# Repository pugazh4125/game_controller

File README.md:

here in this project i have designed my own game controller i wanted to buy a game controller like xbox or ps3 controller but i cant afford those so then began to think how about designing my own controller and that's  how this project was began also doing this project i learnt multi layer pcb designing and also something power traces and signal traces where the traces have to get importantly designed so i learnt them also this project was not completed 100% at first i thought i completed it but i didn't i have to make some changes so i will update this repo once i completed the changes

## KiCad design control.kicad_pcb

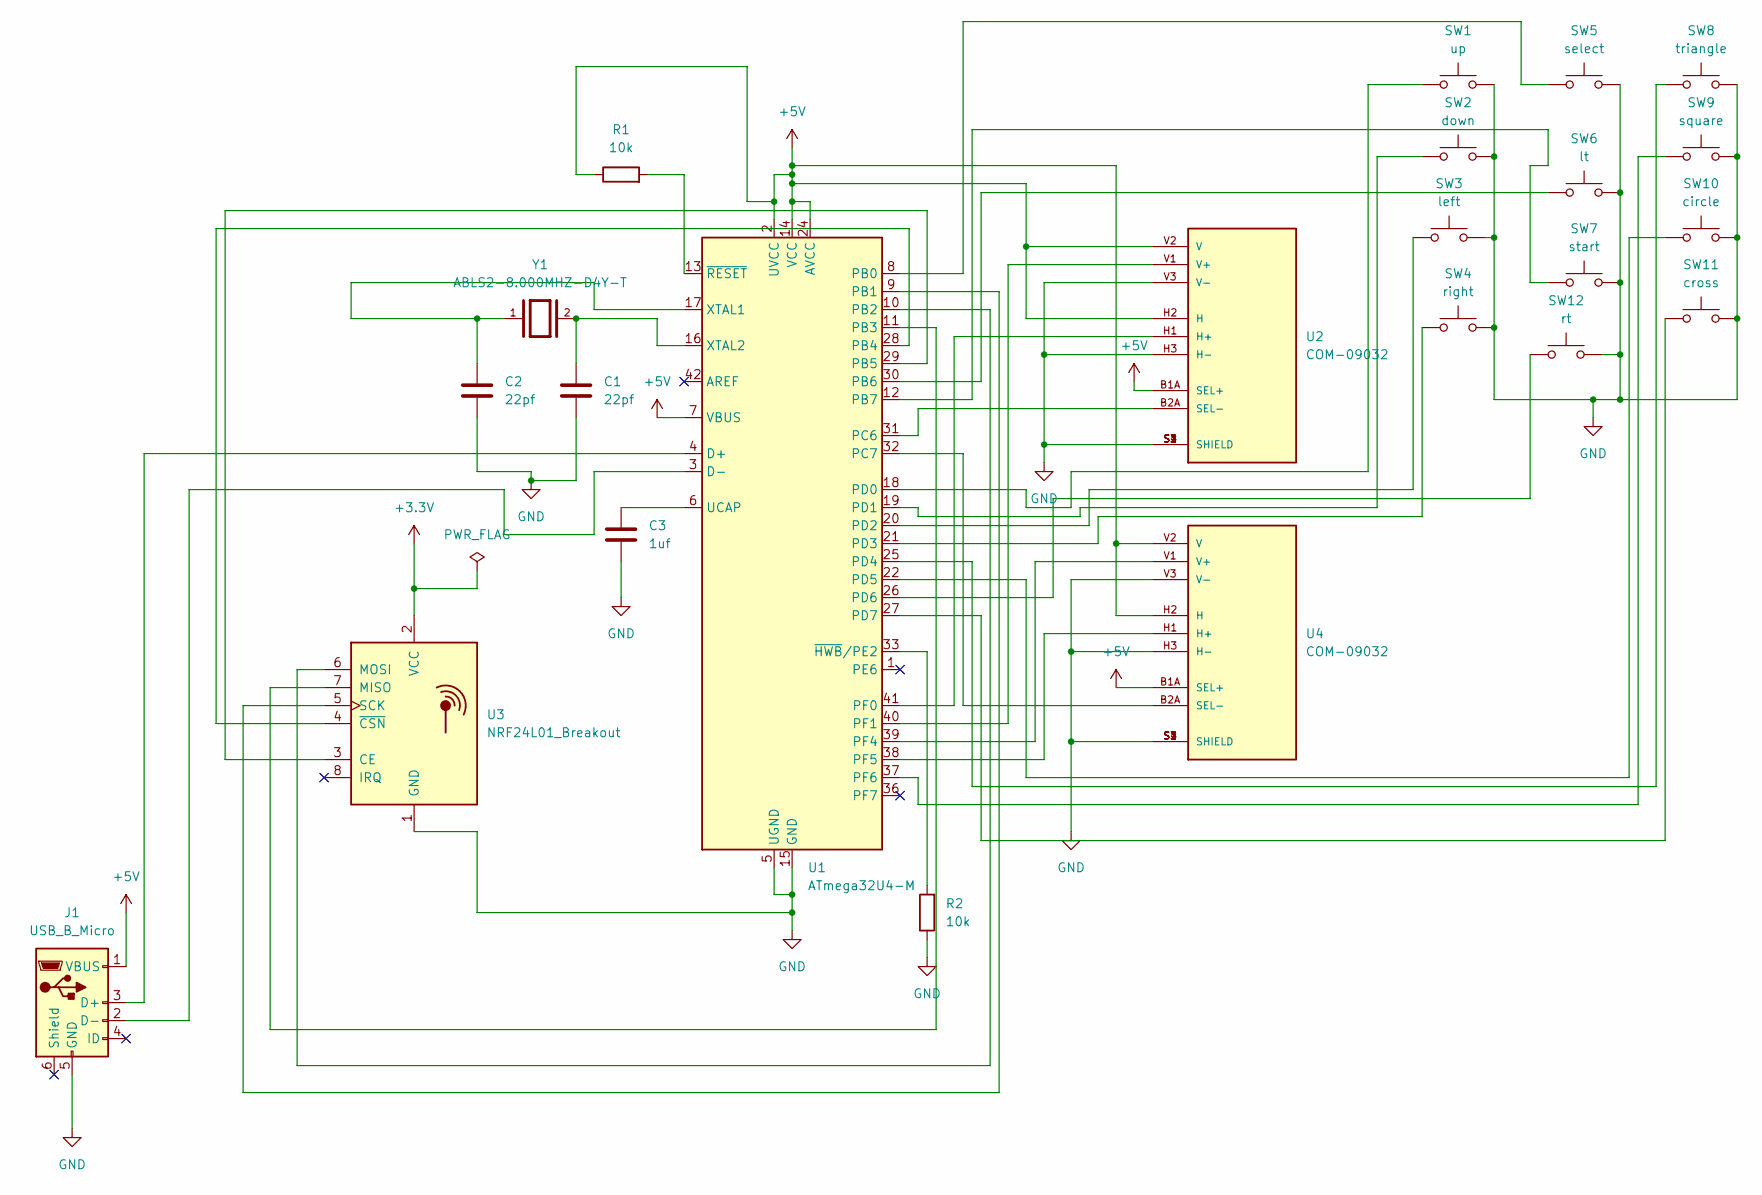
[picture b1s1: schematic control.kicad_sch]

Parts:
C1, C2: 22pf; CP_Radial_D5.0mm_P2.00mm
C3: 1uf; CP_Radial_D5.0mm_P2.00mm
J1: USB_B_Micro; USB_Micro-B_Molex-105017-0001
R1, R2: 10k; R_Axial_DIN0207_L6.3mm_D2.5mm_P15.24mm_Horizontal
SW1: up; SW_PUSH_6mm_H9.5mm
SW2: down; SW_PUSH_6mm_H9.5mm
SW3: left; SW_PUSH_6mm_H9.5mm
SW4: right; SW_PUSH_6mm_H9.5mm
SW5: select; SW_PUSH_6mm_H9.5mm
SW6: lt; SW_PUSH_6mm_H9.5mm
SW7: start; SW_PUSH_6mm_H9.5mm
SW8: triangle; SW_PUSH_6mm_H9.5mm
SW9: square; SW_PUSH_6mm_H9.5mm
SW10: circle; SW_PUSH_6mm_H9.5mm
SW11: cross; SW_PUSH_6mm_H9.5mm
SW12: rt; SW_PUSH_6mm_H9.5mm
U1: ATmega32U4-M; QFN-44-1EP_7x7mm_P0.5mm_EP5.2x5.2mm
U2, U4: COM-09032; XDCR_COM-09032; PARTREV N/A
U3: NRF24L01_Breakout; nRF24L01_Breakout
Y1: ABLS2-8.000MHZ-D4Y-T; XTAL_ABLS2-8.000MHZ-D4Y-T; PARTREV 11.15.2016

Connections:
+3.3V: U3.2 (VCC)
+5V: J1.1 (VBUS), R1.1, U1.2 (UVCC), U1.7 (VBUS), U1.14 (VCC), U1.24 (AVCC), U1.34 (VCC), U1.44 (AVCC), U2.B1A (SEL+), U2.H2 (H), U2.V2 (V), U4.B1A (SEL+), U4.H2 (H), U4.V2 (V)
GND: C1.2, C2.2, C3.2, J1.5 (GND), R2.1, SW1.2, SW2.2, SW3.2, SW4.2, SW5.2, SW6.2, SW7.2, SW8.2, SW9.2, SW10.2, SW11.2, SW12.2, U1.5 (UGND), U1.15 (GND), U1.23 (GND), U1.35 (GND), U1.43 (GND), U1.45 (GND), U2.H3 (H-), U2.S1 (SHIELD), U2.S2 (SHIELD), U2.S3 (SHIELD), U2.S4 (SHIELD), U2.V3 (V-), U3.1 (GND), U4.H3 (H-), U4.S1 (SHIELD), U4.S2 (SHIELD), U4.S3 (SHIELD), U4.S4 (SHIELD), U4.V3 (V-)
unnamed: J1.3 (D+), U1.4 (D+)
unnamed: J1.2 (D-), U1.3 (D-)
unnamed: SW5.1, U1.8 (PB0)
unnamed: U1.9 (PB1), U3.5 (SCK)
unnamed: U1.10 (PB2), U3.6 (MOSI)
unnamed: U1.11 (PB3), U3.7 (MISO)
unnamed: U1.28 (PB4), U3.4 (~CSN)
unnamed: U1.29 (PB5), U3.3 (CE)
unnamed: SW6.1, U1.30 (PB6)
unnamed: SW7.1, U1.12 (PB7)
unnamed: U1.31 (PC6), U2.B2A (SEL-)
unnamed: U1.32 (PC7), U4.B2A (SEL-)
unnamed: SW1.1, U1.18 (PD0)
unnamed: SW2.1, U1.19 (PD1)
unnamed: SW3.1, U1.20 (PD2)
unnamed: SW4.1, U1.21 (PD3)
unnamed: SW8.1, U1.25 (PD4)
unnamed: SW10.1, U1.22 (PD5)
unnamed: SW12.1, U1.26 (PD6)
unnamed: SW11.1, U1.27 (PD7)
unnamed: U1.41 (PF0), U2.H1 (H+)
unnamed: U1.40 (PF1), U2.V1 (V+)
unnamed: U1.39 (PF4), U4.V1 (V+)
unnamed: U1.38 (PF5), U4.H1 (H+)
unnamed: SW9.1, U1.37 (PF6)
unnamed: C3.1, U1.6 (UCAP)
unnamed: C2.1, U1.17 (XTAL1), Y1.1
unnamed: C1.1, U1.16 (XTAL2), Y1.2
unnamed: R2.2, U1.33 (~HWB/PE2)
unnamed: R1.2, U1.13 (~RESET)

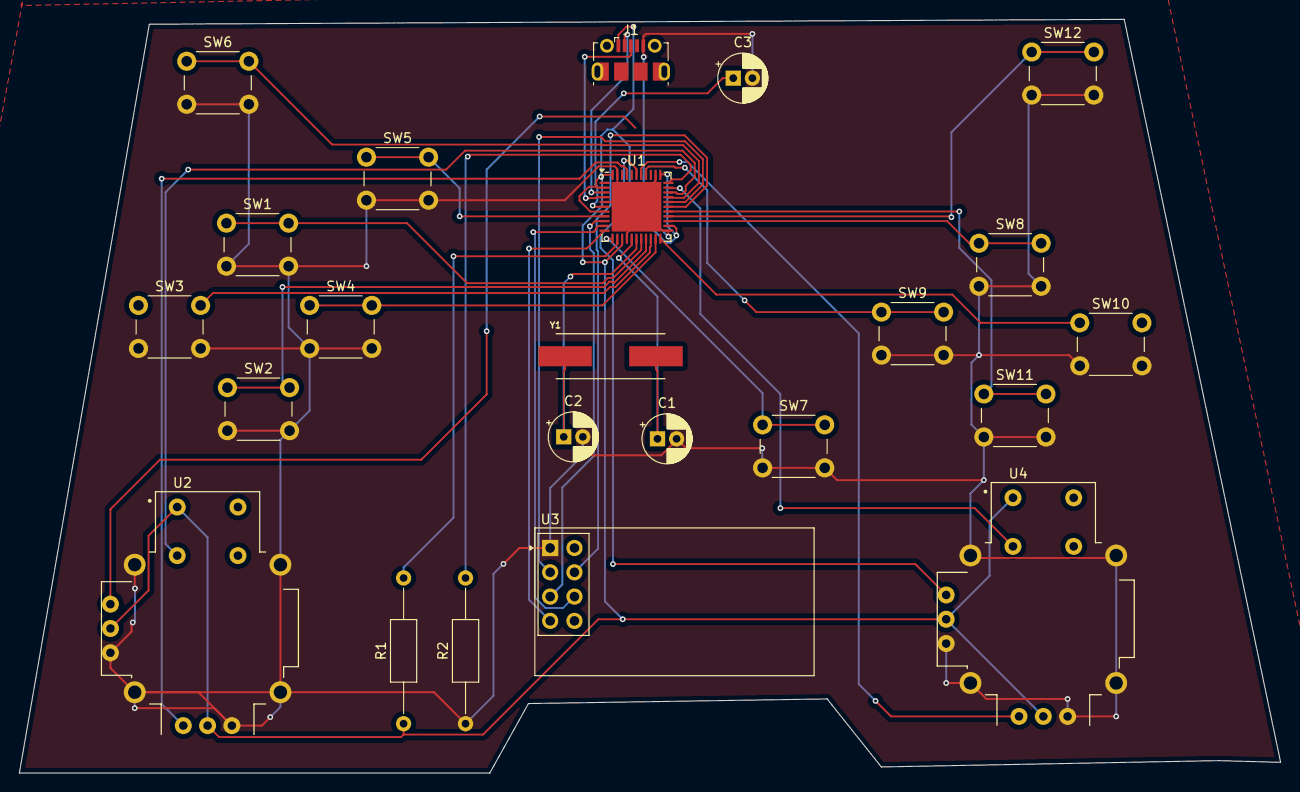
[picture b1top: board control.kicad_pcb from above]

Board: 2 copper layers, 131.9 x 78.8 mm, 23 parts (0 on the bottom side), 32 nets.

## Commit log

2025-05-07 Add files via upload
    So here in this project i designed my own game controller which was began when i was thinking on playing games but i didnt had a joystick yeah i can play games on keyboard also but i wanted to play g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
